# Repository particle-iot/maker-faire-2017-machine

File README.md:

# Maker Faire Machine

Welcome friends! Put all the amazing code, diagrams, PCB files and other
artifacts needed to build the Machine here.

# License

Copyright (C) 2017 Particle Industries Inc
All software code is licensed under the MIT license
All hardware designs are licensed under the Creative Commons Attribution-ShareAlike (CC-BY-SA) license

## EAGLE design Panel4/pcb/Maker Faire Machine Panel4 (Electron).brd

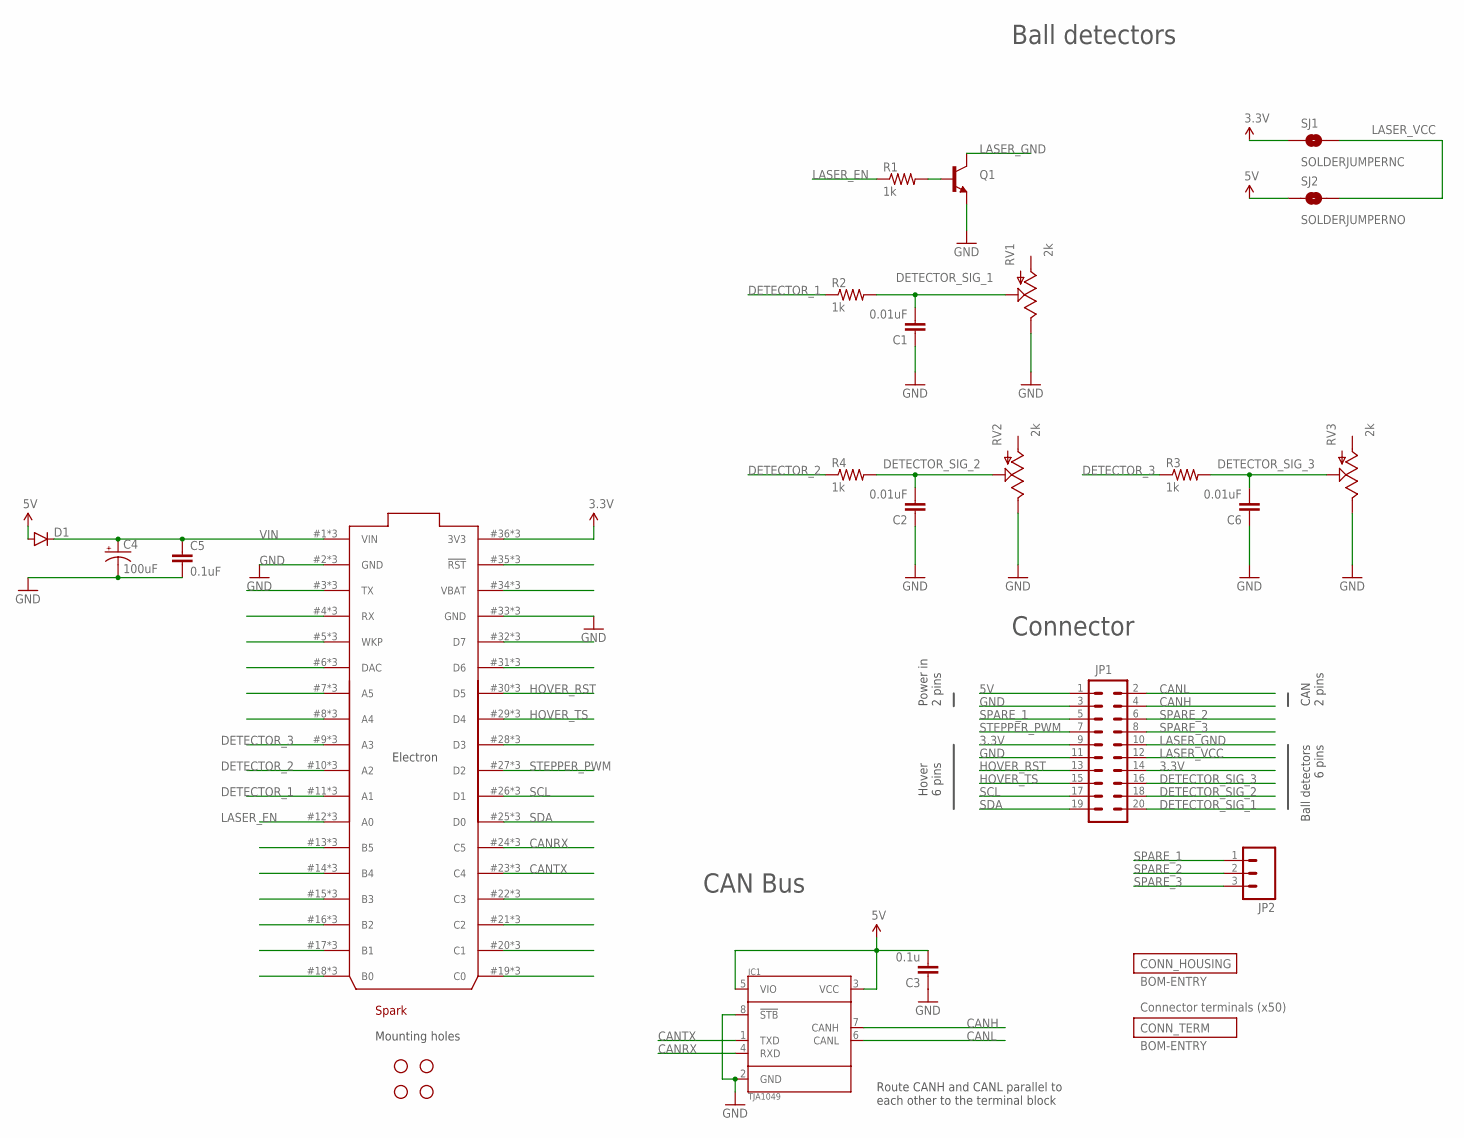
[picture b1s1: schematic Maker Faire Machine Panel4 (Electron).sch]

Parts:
C1, C2, C6: 0.01uF; 1206; PARTNO 12065C103KAT2A
C3: 0.1u; 1206; PARTNO 12065C104KAT2A
C4: 100uF; CPOL-RADIAL-100UF-25V; PARTNO EEU-FM1H101B
C5: 0.1uF; 1206; PARTNO 12065C104KAT2A
D1: DIODESMA; SMA-DIODE; PARTNO B230A-13-F
ELECTRON: ELECTRON_WITH_STACKABLE_HEADERS; ELECTRON_STACKABLE
IC1: TJA1049; SO8; PARTNO TJA1049T-118
JP1: M10X2_MMOLEX_MX150; 2X10_MOLEX_MX150; PARTNO 348302001
JP2: M031X03_NO_SILK; 1X03_NO_SILK
Q1: TRANSISTOR_NPNTO-92-AMMO; TO-92-AMMO; PARTNO PN2222ABU
R1, R2, R3, R4: 1k; 1206; PARTNO ERJ-8ENF1001V
RV1, RV2, RV3: 2k; 3362U; PARTNO 3362U-1-202LF
SJ1: SOLDERJUMPERNC; SJ_2S
SJ2: SOLDERJUMPERNO; SJ_2S-NO
STANDOFF1, STANDOFF2, STANDOFF3, STANDOFF4: STAND-OFF
U$2: SPARK_LOGOSILK; SPARK_LOGO_SILK

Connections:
3.3V: ELECTRON.36 (3V3), ELECTRON.#36 (3V3), ELECTRON.@36 (3V3), JP1.9, JP1.14, SJ1.1
5V: C3.2, D1.A, IC1.3 (VCC), IC1.5 (VIO), JP1.1, SJ2.1
CANH: IC1.7 (CANH), JP1.4
CANL: IC1.6 (CANL), JP1.2
CANRX: ELECTRON.24 (C5), ELECTRON.#24 (C5), ELECTRON.@24 (C5), IC1.4 (RXD)
CANTX: ELECTRON.23 (C4), ELECTRON.#23 (C4), ELECTRON.@23 (C4), IC1.1 (TXD)
DETECTOR_1: ELECTRON.11 (A1), ELECTRON.#11 (A1), ELECTRON.@11 (A1), R2.1
DETECTOR_2: ELECTRON.10 (A2), ELECTRON.#10 (A2), ELECTRON.@10 (A2), R4.1
DETECTOR_3: ELECTRON.9 (A3), ELECTRON.#9 (A3), ELECTRON.@9 (A3), R3.1
DETECTOR_SIG_1: C1.2, JP1.20, R2.2, RV1.P$2 (S)
DETECTOR_SIG_2: C2.2, JP1.18, R4.2, RV2.P$2 (S)
DETECTOR_SIG_3: C6.2, JP1.16, R3.2, RV3.P$2 (S)
GND: C1.1, C2.1, C3.1, C4.2 (-), C5.2, C6.1, ELECTRON.2 (GND), ELECTRON.33 (GND), ELECTRON.#2 (GND), ELECTRON.#33 (GND), ELECTRON.@2 (GND), ELECTRON.@33 (GND), IC1.2 (GND), IC1.8 (!STB), JP1.3, JP1.11, Q1.1 (E), RV1.P$1 (E), RV2.P$1 (E), RV3.P$1 (E)
HOVER_RST: ELECTRON.30 (D5), ELECTRON.#30 (D5), ELECTRON.@30 (D5), JP1.13
HOVER_TS: ELECTRON.29 (D4), ELECTRON.#29 (D4), ELECTRON.@29 (D4), JP1.15
LASER_EN: ELECTRON.12 (A0), ELECTRON.#12 (A0), ELECTRON.@12 (A0), R1.1
LASER_GND: JP1.10, Q1.3 (C)
LASER_VCC: JP1.12, SJ1.2, SJ2.2
unnamed: ELECTRON.35 (!RST), ELECTRON.#35 (!RST), ELECTRON.@35 (!RST)
unnamed: ELECTRON.34 (VBAT), ELECTRON.#34 (VBAT), ELECTRON.@34 (VBAT)
unnamed: Q1.2 (B), R1.2
unnamed: ELECTRON.32 (D7), ELECTRON.#32 (D7), ELECTRON.@32 (D7)
unnamed: ELECTRON.31 (D6), ELECTRON.#31 (D6), ELECTRON.@31 (D6)
unnamed: ELECTRON.28 (D3), ELECTRON.#28 (D3), ELECTRON.@28 (D3)
unnamed: ELECTRON.8 (A4), ELECTRON.#8 (A4), ELECTRON.@8 (A4)
unnamed: ELECTRON.7 (A5), ELECTRON.#7 (A5), ELECTRON.@7 (A5)
unnamed: ELECTRON.6 (DAC), ELECTRON.#6 (DAC), ELECTRON.@6 (DAC)
unnamed: ELECTRON.5 (WKP), ELECTRON.#5 (WKP), ELECTRON.@5 (WKP)
unnamed: ELECTRON.4 (RX), ELECTRON.#4 (RX), ELECTRON.@4 (RX)
unnamed: ELECTRON.3 (TX), ELECTRON.#3 (TX), ELECTRON.@3 (TX)
unnamed: ELECTRON.22 (C3), ELECTRON.#22 (C3), ELECTRON.@22 (C3)
unnamed: ELECTRON.21 (C2), ELECTRON.#21 (C2), ELECTRON.@21 (C2)
unnamed: ELECTRON.20 (C1), ELECTRON.#20 (C1), ELECTRON.@20 (C1)
unnamed: ELECTRON.19 (C0), ELECTRON.#19 (C0), ELECTRON.@19 (C0)
unnamed: ELECTRON.18 (B0), ELECTRON.#18 (B0), ELECTRON.@18 (B0)
unnamed: ELECTRON.17 (B1), ELECTRON.#17 (B1), ELECTRON.@17 (B1)
unnamed: ELECTRON.16 (B2), ELECTRON.#16 (B2), ELECTRON.@16 (B2)
unnamed: ELECTRON.15 (B3), ELECTRON.#15 (B3), ELECTRON.@15 (B3)
unnamed: ELECTRON.14 (B4), ELECTRON.#14 (B4), ELECTRON.@14 (B4)
unnamed: ELECTRON.13 (B5), ELECTRON.#13 (B5), ELECTRON.@13 (B5)
SCL: ELECTRON.26 (D1), ELECTRON.#26 (D1), ELECTRON.@26 (D1), JP1.17
SDA: ELECTRON.25 (D0), ELECTRON.#25 (D0), ELECTRON.@25 (D0), JP1.19
SPARE_1: JP1.5, JP2.1
SPARE_2: JP1.6, JP2.2
SPARE_3: JP1.8, JP2.3
STEPPER_PWM: ELECTRON.27 (D2), ELECTRON.#27 (D2), ELECTRON.@27 (D2), JP1.7
VIN: C4.1 (+), C5.1, D1.C, ELECTRON.1 (VIN), ELECTRON.#1 (VIN), ELECTRON.@1 (VIN)

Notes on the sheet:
Route CANH and CANL parallel to each other to the terminal block
Ball detectors
Hover 6 pins
CAN 2 pins
Ball detectors 6 pins
Connector
CAN Bus
Mounting holes
Power in 2 pins

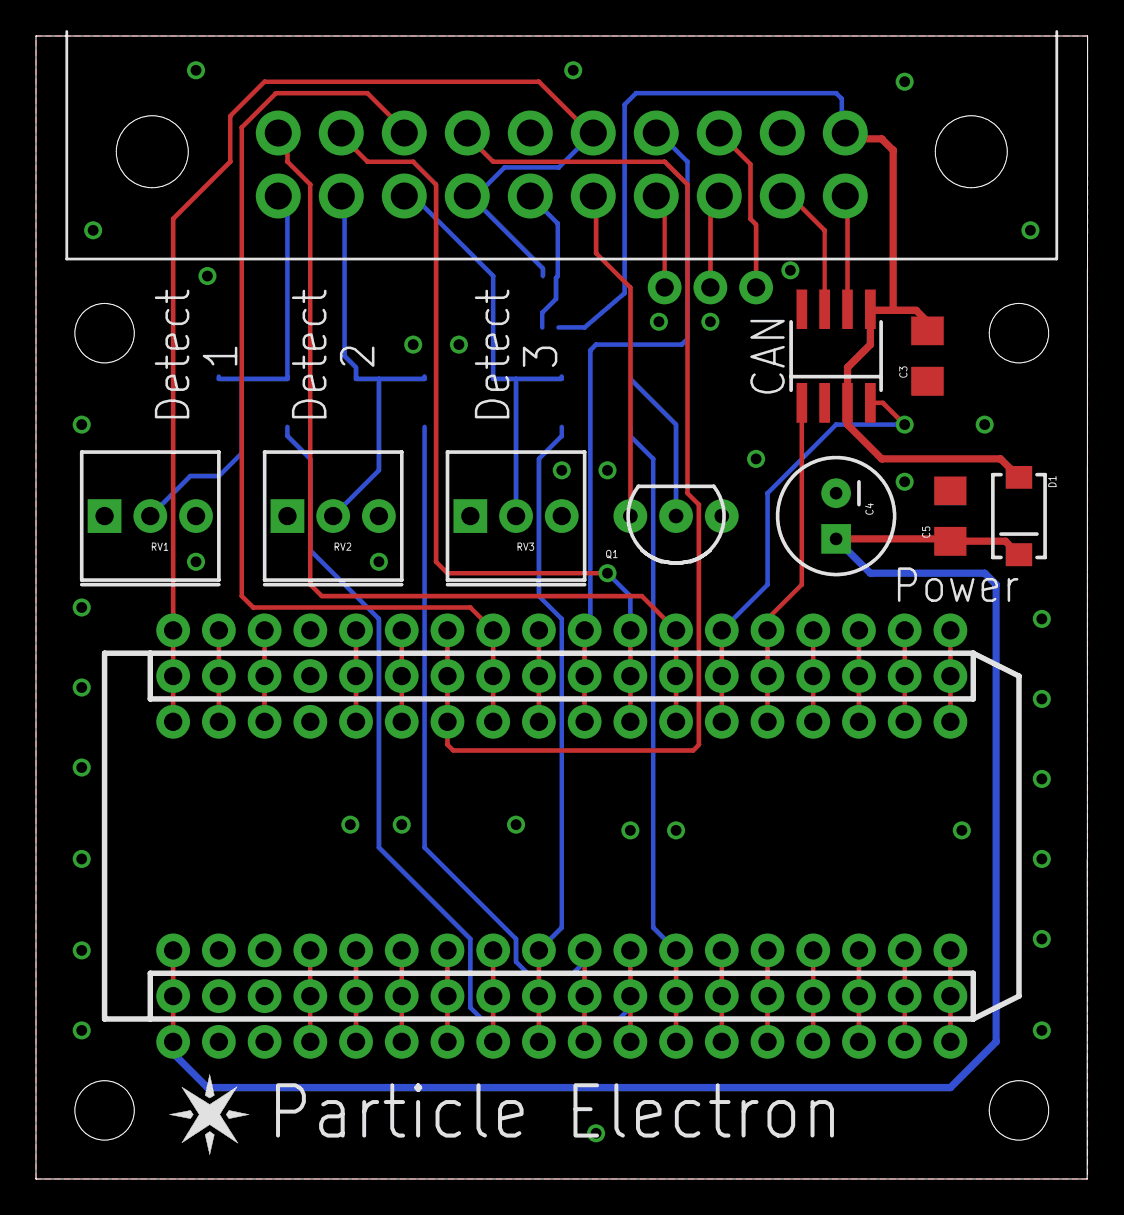
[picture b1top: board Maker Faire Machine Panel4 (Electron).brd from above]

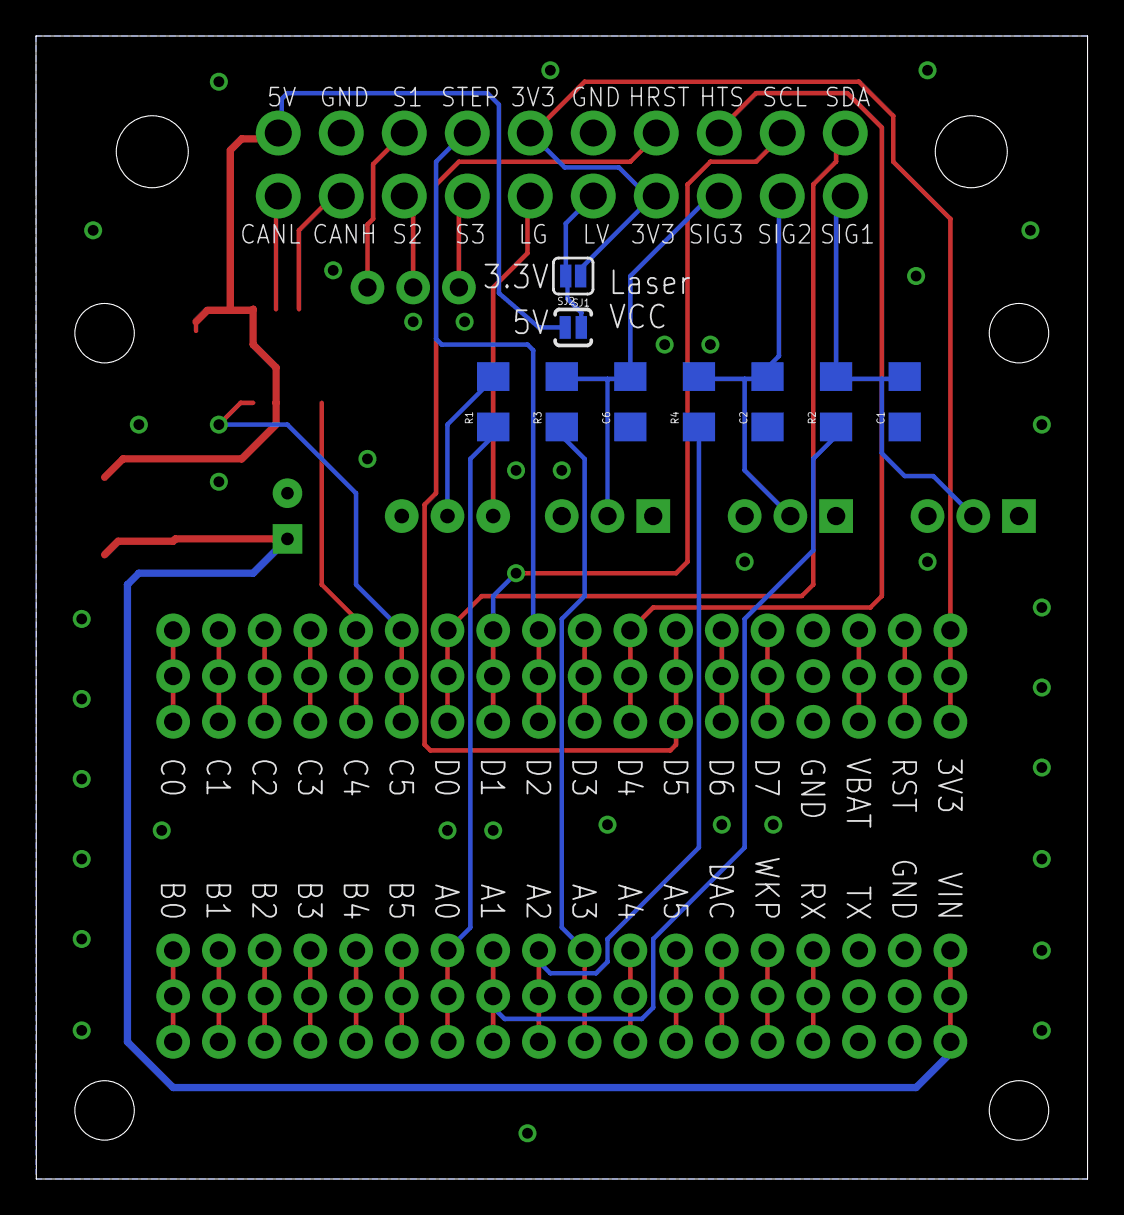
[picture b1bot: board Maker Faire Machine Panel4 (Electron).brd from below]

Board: 2 copper layers, 58.4 x 63.5 mm, 26 parts (9 on the bottom side), 47 nets.

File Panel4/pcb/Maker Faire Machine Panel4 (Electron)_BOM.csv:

Qty-1,Part References,Value,Package,Mfg Part Num,Mfg Name,VID,Vendor Part Num,Description,XREF
0,JP2(DNP),,1X03_NO_SILK,***PART# '*' NOT FOUND***,*,*,*,*,*
1,JP1,,2X10_MOLEX_MX150,348302001,Molex,DK,WM12752-ND,MX150 RA HDR 2X10 ST BLK KEY A,REF77
1,D1,,SMA-DIODE,B230A-13-F,Diodes-Incorporated,DK,B230A-FDICT-ND,DIODE SCHOTTKY 30V 2A SMA,REF43
1,Q1,,TO-92-AMMO,PN2222ABU,Fairchild Semiconductor ,DK,PN2222AFS-ND,TRANSISTOR NPN TO92,REF75
2,"C3, C5",0.1uF,1206,12065C104KAT2A,AVX,DK,478-1556-1-ND,CERAMIC CAPACITOR 0.1UF 50V X7R 10% 1206,REF61
3,"C1, C2, C6",0.01uF,1206,12065C103KAT2A,AVX,DK,478-1542-1-ND,MLCC CAPACITOR 0.01uF 50V X7R 10% 1206 FULL REEL,REF62
4,"R1, R2, R3, R4",1k,1206,ERJ-8ENF1001V,Panasonic,DK,P1.00KFCT-ND,RES SMD 1K OHM 1% 1/4W 1206,REF74
3,"RV1, RV2, RV3",2k,3362U,3362U-1-202LF,Bourns Inc.,DK,3362U-202LF-ND,TRIMMER 2K OHM 0.5W PC PIN,REF72
1,C4,100uF,CPOL-RADIAL-100UF-25V,EEU-FM1H101B,Panasonic Electronic Components,DK,P19712CT-ND,CAP ALUM 100UF 20% 50V RADIAL,REF76
50,CONN_TERM,BOM-ENTRY,*,330122002,Molex,DK,WM3687CT-ND,TERM RCPT TIN 18-20AWG SLD,REF79
1,CONN_HOUSING,BOM-ENTRY,*,334722001,Molex,DK,WM4737-ND,CONN RCPT 20POS DUAL BLACK,REF78
1,ELECTRON,ELECTRON_WITH_STACKABLE_HEADERS,ELECTRON_STACKABLE,***PART# '*' NOT FOUND***,*,*,*,*,*
1,IC1,TJA1049,SO8,TJA1049T-118,NXP Semiconductors,DK,568-8682-1-ND,IC CAN TRANSEIVER HS 8SOIC,REF16

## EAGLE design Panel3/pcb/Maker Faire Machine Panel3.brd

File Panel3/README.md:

# Panel 3

**Sensor:** Rotary encoder (quadrature)
**Mechanism:** ball lifter with multiple paths/runs
**Story:** Particle cloud routes and delivers the data internally

[See spreadsheet](https://docs.google.com/spreadsheets/d/1myQVK4iyX1niJGtPiAOqu2GMmV2cjAntq5kpxnjmFF0/edit#gid=340408367)
for more info.

## TOC

* Mechanical drawings
* BOM
* PCB
* Firmware
* Tweakable parameters

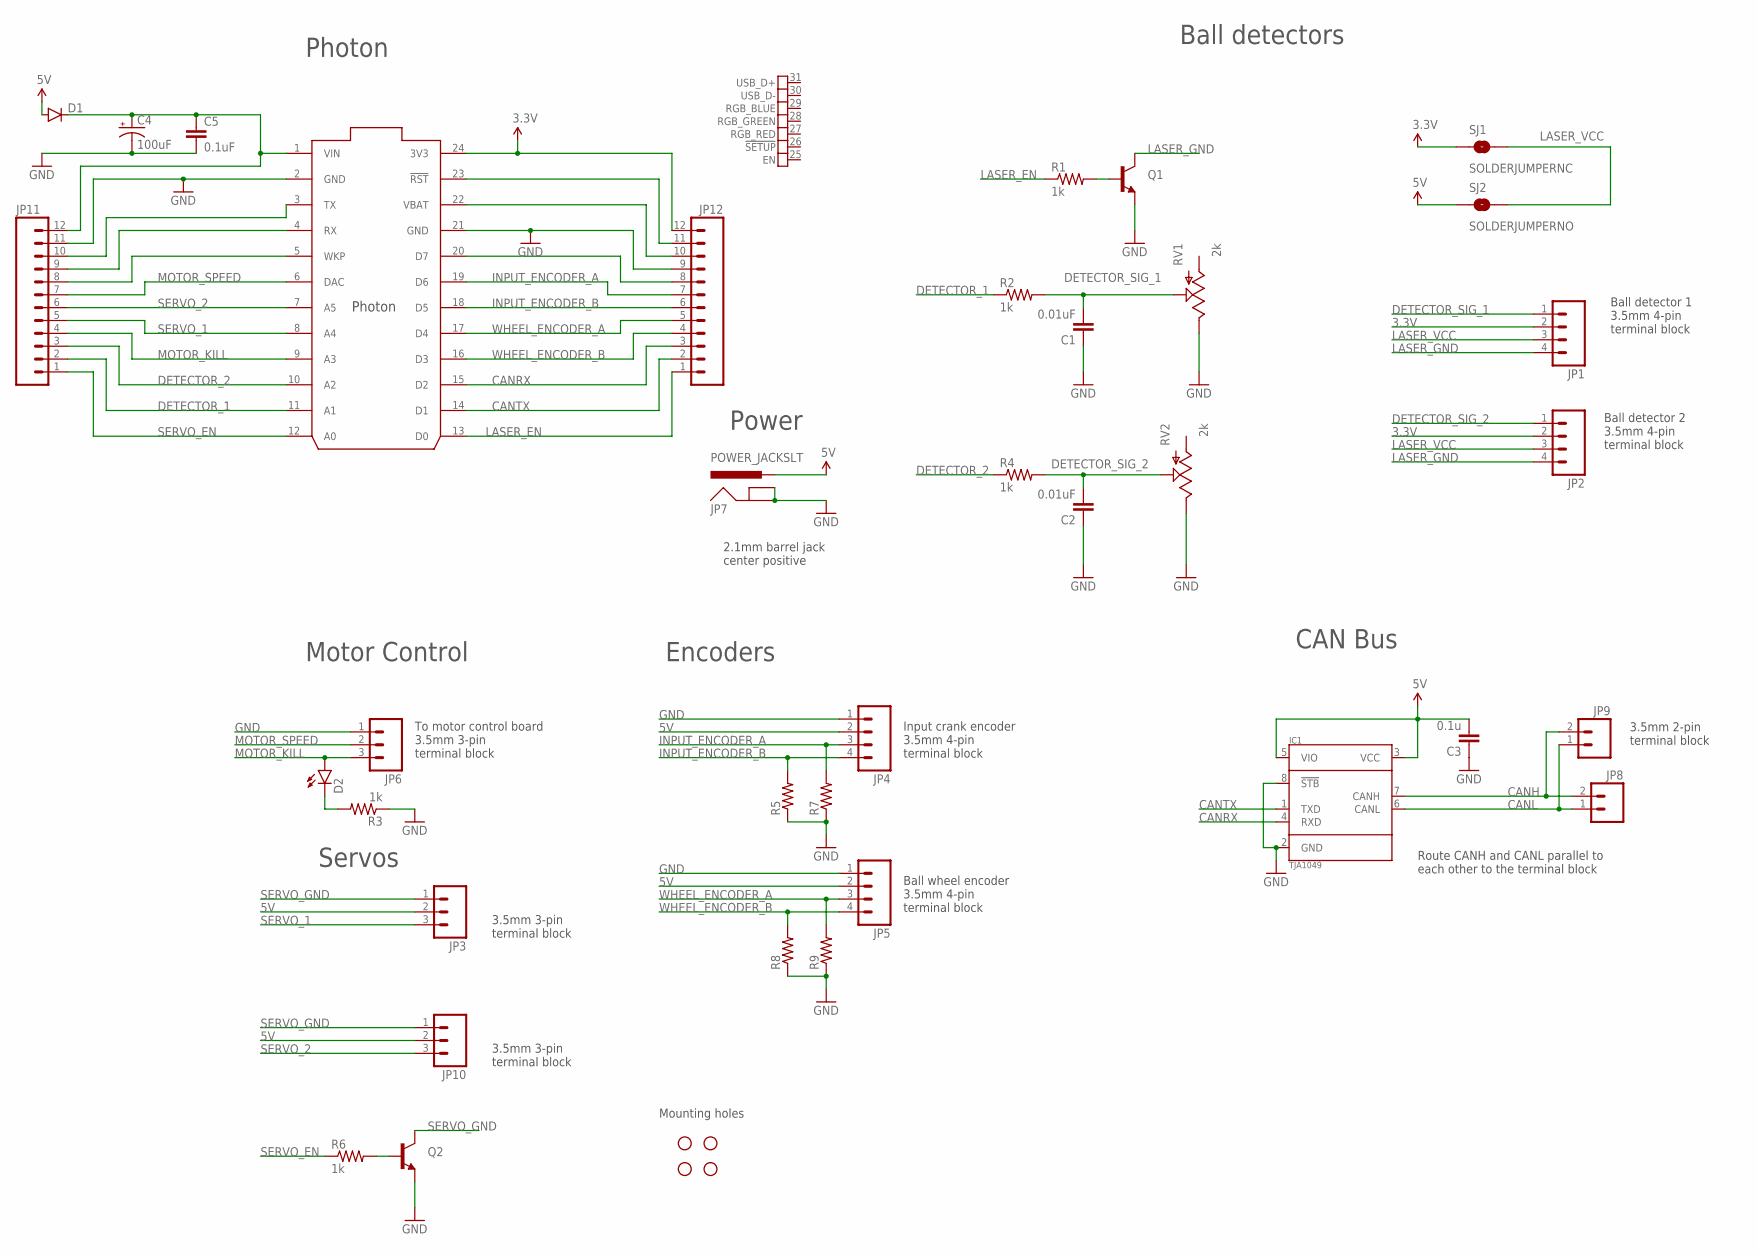
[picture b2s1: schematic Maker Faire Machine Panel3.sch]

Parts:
C1, C2: 0.01uF; 1206; PARTNO 12065C103KAT2A
C3: 0.1u; 1206; PARTNO 12065C104KAT2A
C4: 100uF; CPOL-RADIAL-100UF-25V; PARTNO EEU-FM1H101B
C5: 0.1uF; 1206; PARTNO 12065C104KAT2A
D1: DIODESMA; SMA-DIODE; PARTNO B230A-13-F
D2: LED5MM; PARTNO SSL-LX5093HD
IC1: TJA1049; SO8; PARTNO TJA1049T-118
JP1, JP2, JP4: M04SCREW; SCREWTERMINAL-3.5MM-4; PARTNO OSTTE040104
JP3, JP6: M03SCREW; SCREWTERMINAL-3.5MM-3; PARTNO OSTTE020104
JP5: M04SCREW; SCREWTERMINAL-3.5MM-4; PARTNO OSTTE030104
JP7: POWER_JACKSLT; POWER_JACK_SLOT; PARTNO PJ-202A
JP8, JP9: M023.5MM; SCREWTERMINAL-3.5MM-2; PARTNO OSTTE020104
JP10: M03SCREW; SCREWTERMINAL-3.5MM-3; PARTNO OSTTE030104
JP11, JP12: M12NO_SILK; 1X12_NO_SILK
Q1, Q2: TRANSISTOR_NPNTO-92-AMMO; TO-92-AMMO; PARTNO PN2222ABU
R1, R2, R3, R4, R6: 1k; 1206; PARTNO ERJ-8ENF1001V
R5, R7, R8, R9: RESISTORKIT; AXIAL-0.3-KIT
RV1, RV2: 2k; 3362U; PARTNO 3362U-1-202LF
SJ1: SOLDERJUMPERNC; SJ_2S
SJ2: SOLDERJUMPERNO; SJ_2S-NO
STANDOFF1, STANDOFF2, STANDOFF3, STANDOFF4: STAND-OFF
U$1: PHOTON_SMD

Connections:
3.3V: JP1.2, JP2.2, JP12.12, SJ1.1, U$1.24 (3V3)
5V: C3.2, D1.A, IC1.3 (VCC), IC1.5 (VIO), JP3.2, JP4.2, JP5.2, JP7.PWR, JP10.2, SJ2.1
CANH: IC1.7 (CANH), JP8.2, JP9.2
CANL: IC1.6 (CANL), JP8.1, JP9.1
CANRX: IC1.4 (RXD), JP12.3, U$1.15 (D2)
CANTX: IC1.1 (TXD), JP12.2, U$1.14 (D1)
DETECTOR_1: JP11.2, R2.1, U$1.11 (A1)
DETECTOR_2: JP11.3, R4.1, U$1.10 (A2)
DETECTOR_SIG_1: C1.2, JP1.1, R2.2, RV1.P$2 (S)
DETECTOR_SIG_2: C2.2, JP2.1, R4.2, RV2.P$2 (S)
GND: C1.1, C2.1, C3.1, C4.2 (-), C5.2, IC1.2 (GND), IC1.8 (!STB), JP4.1, JP5.1, JP6.1, JP7.GND@1 (GNDBREAK), JP7.GND@2 (GND), JP11.11, JP12.9, Q1.1 (E), Q2.1 (E), R3.1, R5.P$1 (1), R7.P$1 (1), R8.P$1 (1), R9.P$1 (1), RV1.P$1 (E), RV2.P$1 (E), U$1.2 (GND), U$1.21 (GND)
INPUT_ENCODER_A: JP4.3, JP12.7, R7.P$2 (2), U$1.19 (D6)
INPUT_ENCODER_B: JP4.4, JP12.6, R5.P$2 (2), U$1.18 (D5)
LASER_EN: JP12.1, R1.1, U$1.13 (D0)
LASER_GND: JP1.4, JP2.4, Q1.3 (C)
LASER_VCC: JP1.3, JP2.3, SJ1.2, SJ2.2
MOTOR_KILL: D2.A, JP6.3, JP11.4, U$1.9 (A3)
MOTOR_SPEED: JP6.2, JP11.7, U$1.6 (DAC)
unnamed: Q1.2 (B), R1.2
unnamed: Q2.2 (B), R6.2
unnamed: D2.K (C), R3.2
unnamed: JP12.8, U$1.20 (D7)
unnamed: JP12.10, U$1.22 (VBAT)
unnamed: JP12.11, U$1.23 (!RST)
RX: JP11.9, U$1.4 (RX)
SERVO_1: JP3.3, JP11.5, U$1.8 (A4)
SERVO_2: JP10.3, JP11.6, U$1.7 (A5)
SERVO_EN: JP11.1, R6.1, U$1.12 (A0)
SERVO_GND: JP3.1, JP10.1, Q2.3 (C)
TX: JP11.10, U$1.3 (TX)
VIN: C4.1 (+), C5.1, D1.C, JP11.12, U$1.1 (VIN)
WHEEL_ENCODER_A: JP5.3, JP12.5, R9.P$2 (2), U$1.17 (D4)
WHEEL_ENCODER_B: JP5.4, JP12.4, R8.P$2 (2), U$1.16 (D3)
WKP: JP11.8, U$1.5 (WKP)

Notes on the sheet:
Ball detectors
Ball detector 1 3.5mm 4-pin terminal block
Ball detector 2 3.5mm 4-pin terminal block
CAN Bus
Encoders
Route CANH and CANL parallel to each other to the terminal block
Input crank encoder 3.5mm 4-pin terminal block
Ball wheel encoder 3.5mm 4-pin terminal block
Motor Control
To motor control board 3.5mm 3-pin terminal block
Power
2.1mm barrel jack center positive
Photon
Servos
3.5mm 3-pin terminal block
Mounting holes
3.5mm 2-pin terminal block

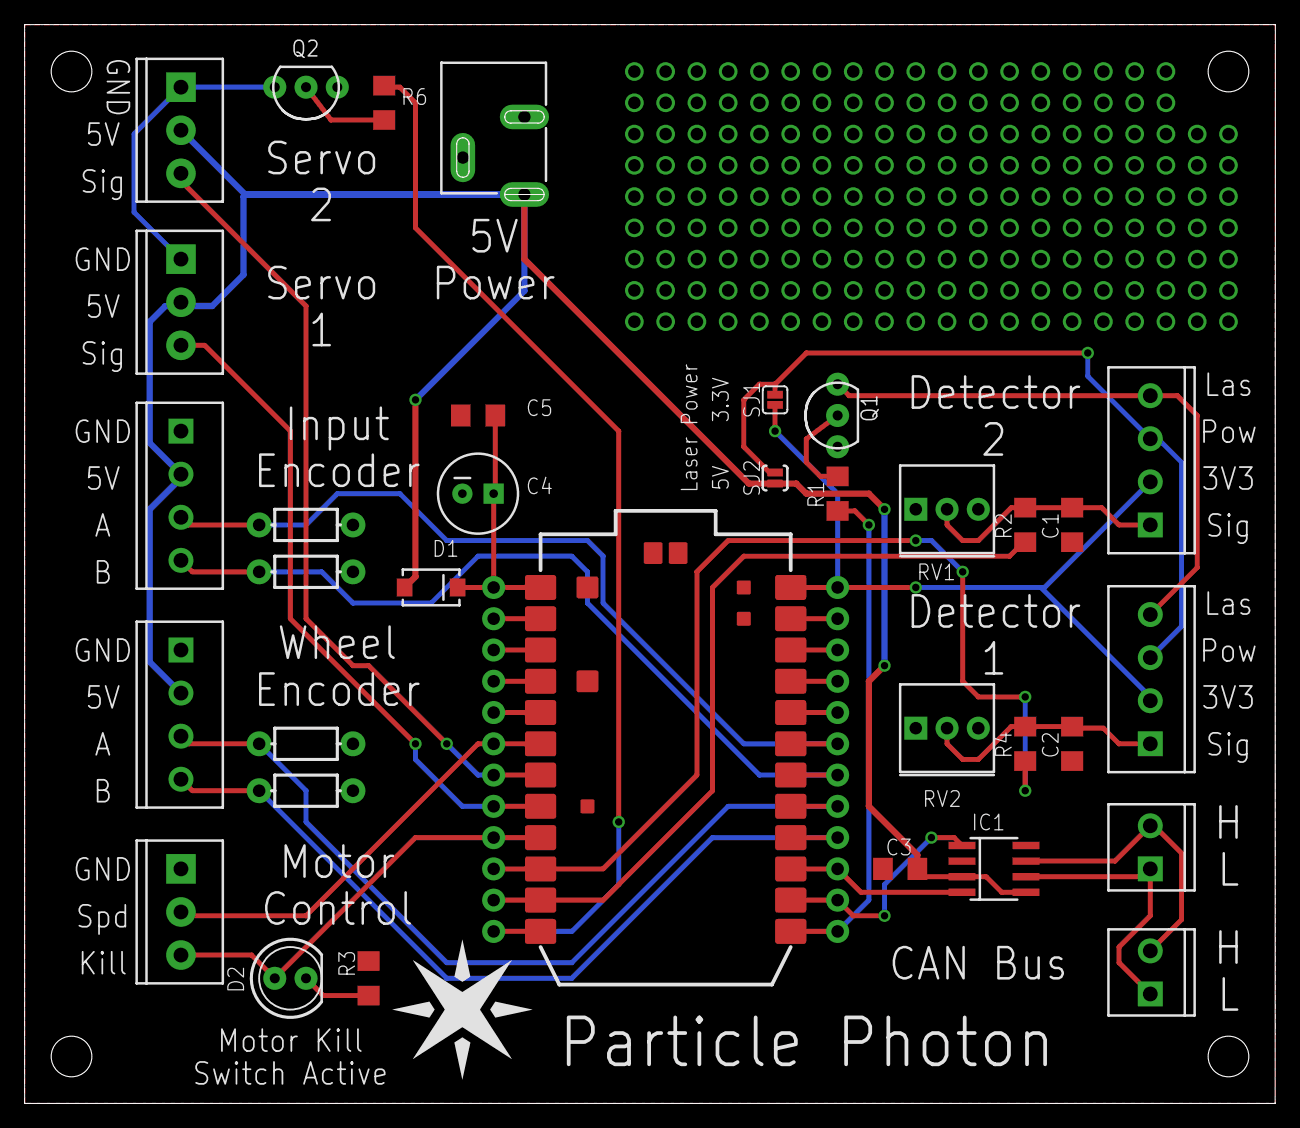
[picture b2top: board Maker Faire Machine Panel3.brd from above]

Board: 2 copper layers, 101.6 x 87.6 mm, 40 parts (0 on the bottom side), 34 nets.

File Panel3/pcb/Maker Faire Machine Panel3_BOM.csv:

Qty-1,Part References,Value,Package,Mfg Part Num,Mfg Name,VID,Vendor Part Num,Description,XREF
1,"D1",,SMA-DIODE,B230A-13-F,Diodes-Incorporated,DK,B230A-FDICT-ND,DIODE SCHOTTKY 30V 2A SMA,REF43
4,"JP3, JP6, JP8, JP9",,SCREWTERMINAL-3.5MM-2,OSTTE020104,On Shore Technology Inc.,DK,ED2740-ND,TERMINAL BLOCK 3.5MM 2POS PCB,REF68
2,"JP10, JP5",,SCREWTERMINAL-3.5MM-4,OSTTE030104,On Shore Technology Inc.,DK,ED2741-ND,TERMINAL BLOCK 3.5MM 3POS PCB,REF69
3,"JP1, JP2, JP4",,SCREWTERMINAL-3.5MM-4,OSTTE040104,On Shore Technology Inc.,DK,ED2742-ND,TERMINAL BLOCK 3.5MM 4POS PCB,REF70
2,"Q1, Q2",,TO-92,PN2222ABU,Fairchild Semiconductor ,DK,PN2222AFS-ND,TRANSISTOR NPN TO92,REF75
1,"D2",,LED5MM,SSL-LX5093HD,Lumex,DK,67-1102-ND,LED RED DIFF 5MM ROUND T/H,REF73
2,"C3, C5",0.1uF,1206,12065C104KAT2A,AVX,DK,478-1556-1-ND,CERAMIC CAPACITOR 0.1UF 50V X7R 10% 1206,REF61
2,"C1, C2",0.01uF,1206,12065C103KAT2A,AVX,DK,478-1542-1-ND,MLCC CAPACITOR 0.01uF 50V X7R 10% 1206 FULL REEL,REF62
5,"R1, R2, R3, R4, R6",1k,1206,ERJ-8ENF1001V,Panasonic,DK,P1.00KFCT-ND,RES SMD 1K OHM 1% 1/4W 1206,REF74
2,"RV1, RV2",2k,3362U,3362U-1-202LF,Bourns Inc.,DK,3362U-202LF-ND,TRIMMER 2K OHM 0.5W PC PIN,REF72
1,"C4",100uF,CPOL-RADIAL-100UF-25V,EEU-FM1H101B,Panasonic Electronic Components,DK,P19712CT-ND,CAP ALUM 100UF 20% 50V RADIAL,REF76
1,"U$1",PHOTON_SMD,PHOTON_SMD,***PART# '*' NOT FOUND***,*,*,*,*,*
1,"JP7",POWER_JACKSLT,POWER_JACK_SLOT,PJ-202A,CUI Inc.,DK,CP-202A-ND,CONN PWR JACK 2X5.5MM KINKED PIN,REF71
1,"IC1",TJA1049,SO8,TJA1049T-118,NXP Semiconductors,DK,568-8682-1-ND,IC CAN TRANSEIVER HS 8SOIC,REF16

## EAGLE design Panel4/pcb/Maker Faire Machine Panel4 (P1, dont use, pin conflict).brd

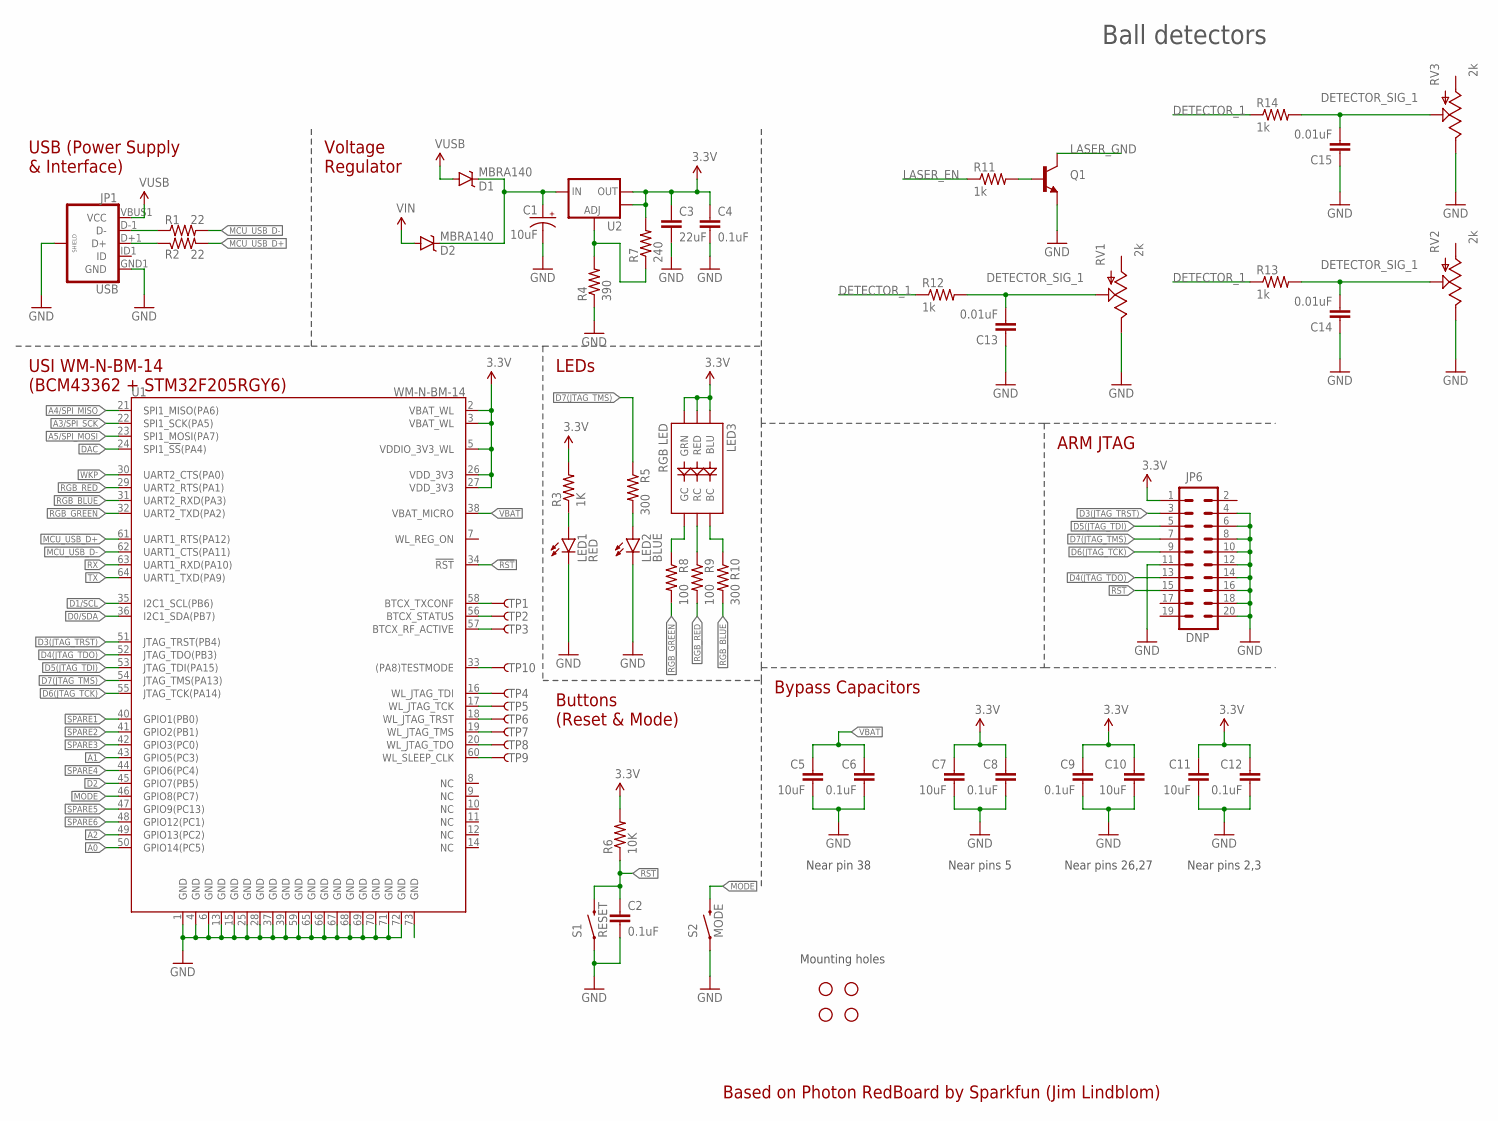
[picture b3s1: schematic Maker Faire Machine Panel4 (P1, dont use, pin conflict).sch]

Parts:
C1: 10uF; EIA3216
C2, C4, C6, C8, C9, C12: 0.1uF; 0603-CAP
C3: 22uF; 0805
C5, C7, C10, C11: 10uF; 0603-CAP
C13, C14, C15: 0.01uF; 1206; PARTNO 12065C103KAT2A
D1, D2: MBRA140; SMA-DIODE
JP1: USB; USB-B-MICRO-SMD_V03
JP6: DNP; 2X10
LED1: RED; LED-1206
LED2: BLUE; LED-1206
LED3: RGB LED; PLCC-6-LED
Q1: TRANSISTOR_NPNSOT89; SOT89; PARTNO PN2222ABU
R1, R2: 22; 0603-RES
R3: 1K; 0603-RES
R4: 390; 0603-RES
R5, R10: 300; 0603-RES
R6: 10K; 0603-RES
R7: 240; 0603-RES
R8, R9: 100; 0603-RES
R11, R12, R13, R14: 1k; 1206; PARTNO ERJ-8ENF1001V
RV1, RV2, RV3: 2k; 3362U; PARTNO 3362U-1-202LF
S1: RESET; TACTILE-PTH
S2: MODE; TACTILE-PTH
STANDOFF1, STANDOFF2, STANDOFF3, STANDOFF4: STAND-OFF
TP1, TP2, TP3, TP4, TP5, TP6, TP7, TP8, TP9, TP10: TEST-POINTTP_15TH_THRU; TP_15TH
U1: WM-N-BM-14
U2: V_REG_LM1117SOT223; SOT223

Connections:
3.3V: C3.1, C4.1, C7.1, C8.1, C9.1, C10.1, C11.1, C12.1, JP6.1, LED3.AB (BLU), LED3.AG (GRN), LED3.AR (RED), R3.2, R6.2, R7.2, U1.2 (VBAT_WL), U1.3 (VBAT_WL), U1.5 (VDDIO_3V3_WL), U1.26 (VDD_3V3), U1.27 (VDD_3V3), U2.2 (OUT), U2.4 (OUT)
!MODE: S2.3 (2), U1.46 (GPIO8(PC7))
!RST: C2.1, JP6.15, R6.1, S1.3 (2), U1.34 (!RST!)
A0: U1.50 (GPIO14(PC5))
A1: U1.43 (GPIO5(PC3))
A2: U1.49 (GPIO13(PC2))
A3/SPI_SCK: U1.22 (SPI1_SCK(PA5))
A4/SPI_MISO: U1.21 (SPI1_MISO(PA6))
A5/SPI_MOSI: U1.23 (SPI1_MOSI(PA7))
BTCX_RF_ACTIVE: TP3.P$1, U1.57 (BTCX_RF_ACTIVE)
BTCX_STATUS: TP2.P$1, U1.56 (BTCX_STATUS)
BTCX_TXCONF: TP1.P$1, U1.58 (BTCX_TXCONF)
D0/SDA: U1.36 (I2C1_SDA(PB7))
D1/SCL: U1.35 (I2C1_SCL(PB6))
D2: U1.45 (GPIO7(PB5))
D3(JTAG_TRST): JP6.3, U1.51 (JTAG_TRST(PB4))
D4(JTAG_TDO): JP6.13, U1.52 (JTAG_TDO(PB3))
D5(JTAG_TDI): JP6.5, U1.53 (JTAG_TDI(PA15))
D6(JTAG_TCK): JP6.9, U1.55 (JTAG_TCK(PA14))
D7(JTAG_TMS): JP6.7, R5.1, U1.54 (JTAG_TMS(PA13))
D+: JP1.D+1 (D+), R2.1
D-: JP1.D-1 (D-), R1.1
DAC: U1.24 (SPI1_!SS!(PA4))
DETECTOR_1: R12.1, R13.1, R14.1
DETECTOR_SIG_1: C13.2, C14.2, C15.2, R12.2, R13.2, R14.2, RV1.P$2 (S), RV2.P$2 (S), RV3.P$2 (S)
GND: C1.C (-), C2.2, C3.2, C4.2, C5.2, C6.2, C7.2, C8.2, C9.2, C10.2, C11.2, C12.2, C13.1, C14.1, C15.1, JP1.GND1 (GND), JP1.SHIELD1 (SHIELD), JP1.SHIELD2 (SHIELD), JP1.SHIELD3 (SHIELD), JP6.4, JP6.6, JP6.8, JP6.10, JP6.11, JP6.12, JP6.14, JP6.16, JP6.18, JP6.20, LED1.C, LED2.C, Q1.3 (E), R4.1, RV1.P$1 (E), RV2.P$1 (E), RV3.P$1 (E), S1.1, S2.1, U1.1 (GND), U1.4 (GND), U1.6 (GND), U1.13 (GND), U1.15 (GND), U1.25 (GND), U1.28 (GND), U1.37 (GND), U1.39 (GND), U1.59 (GND), U1.65 (GND), U1.66 (GND), U1.67 (GND), U1.68 (GND), U1.69 (GND), U1.70 (GND), U1.71 (GND), U1.72 (GND)
LASER_EN: R11.1
LASER_GND: Q1.2 (C)
MCU_USB_D+: R2.2, U1.61 (UART1_RTS(PA12))
MCU_USB_D-: R1.2, U1.62 (UART1_CTS(PA11))
unnamed: TP10.P$1, U1.33 ((PA8)TESTMODE)
unnamed: LED3.CG (GC), R8.1
unnamed: LED3.CR (RC), R9.1
unnamed: LED3.CB (BC), R10.1
unnamed: LED1.A, R3.1
unnamed: LED2.A, R5.2
unnamed: Q1.1 (B), R11.2
unnamed: C1.A (+), D1.C, D2.C, U2.3 (IN)
unnamed: R4.2, R7.1, U2.1 (ADJ)
RGB_BLUE: R10.2, U1.31 (UART2_RXD(PA3))
RGB_GREEN: R8.2, U1.32 (UART2_TXD(PA2))
RGB_RED: R9.2, U1.29 (UART2_RTS(PA1))
RX: U1.63 (UART1_RXD(PA10))
SPARE1: U1.40 (GPIO1(PB0))
SPARE2: U1.41 (GPIO2(PB1))
SPARE3: U1.42 (GPIO3(PC0))
SPARE4: U1.44 (GPIO6(PC4))
SPARE5: U1.47 (GPIO9(PC13))
SPARE6: U1.48 (GPIO12(PC1))
TX: U1.64 (UART1_TXD(PA9))
VBAT: C5.1, C6.1, U1.38 (VBAT_MICRO)
VIN: D2.A
VUSB: D1.A, JP1.VBUS1 (VCC)
WKP: U1.30 (UART2_CTS(PA0))
WL_JTAG_TCK: TP5.P$1, U1.17 (WL_JTAG_TCK)
WL_JTAG_TDI: TP4.P$1, U1.16 (WL_JTAG_TDI)
WL_JTAG_TDO: TP8.P$1, U1.20 (WL_JTAG_TDO)
WL_JTAG_TMS: TP7.P$1, U1.19 (WL_JTAG_TMS)
WL_JTAG_TRST: TP6.P$1, U1.18 (WL_JTAG_TRST)
WL_SLEEP_CLK: TP9.P$1, U1.60 (WL_SLEEP_CLK)

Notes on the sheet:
Near pin 38
Near pins 26,27
Near pins 5
Near pins 2,3
Voltage Regulator
USB (Power Supply & Interface)
ARM JTAG
Bypass Capacitors
LEDs
Buttons (Reset & Mode)
USI WM-N-BM-14 (BCM43362 + STM32F205RGY6)
Based on Photon RedBoard by Sparkfun (Jim Lindblom)
Mounting holes
Ball detectors

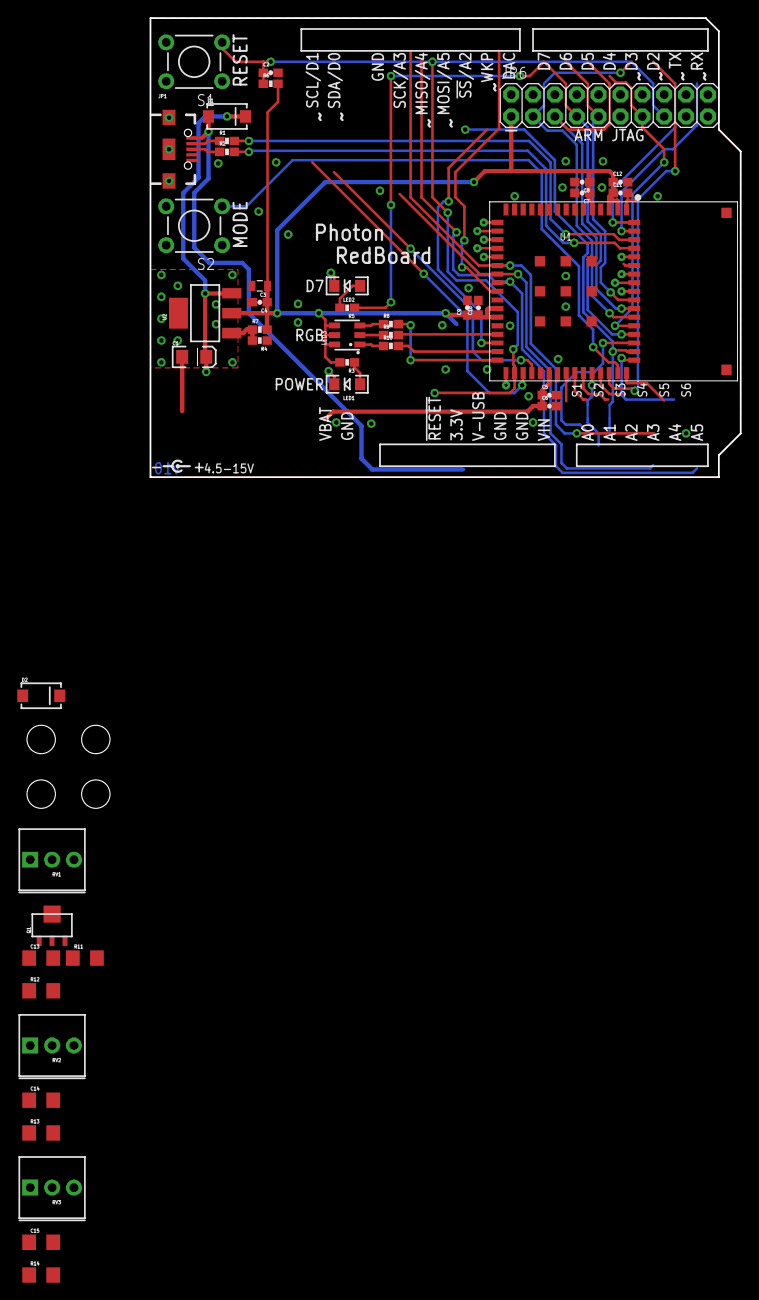
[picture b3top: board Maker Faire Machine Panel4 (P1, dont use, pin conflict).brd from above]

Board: 2 copper layers, 68.6 x 53.3 mm, 58 parts (1 on the bottom side), 38 nets.

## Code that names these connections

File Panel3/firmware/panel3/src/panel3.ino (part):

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const auto BALL_DETECTOR_2_PIN = A1;
const auto BALL_DETECTOR_1_PIN = A2;
const auto BALL_WHEEL_KILL_SWITCH_PIN = A3;
const auto SERVO_1_PIN = A4;
const auto SERVO_2_PIN = A5;
const auto BALL_WHEEL_MOTOR_SPEED_PIN = DAC;
const auto BALL_DETECTOR_3_PIN = WKP;
const auto WHEEL_TURN_PIN = TX;

/*
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 */

const auto MOTOR_RUN = HIGH;
const auto MOTOR_KILL = LOW;

auto motorState = AUTO_START ? MOTOR_RUN : MOTOR_KILL;
uint32_t motorSpeed = 0;
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
void setupMotor() {
  pinMode(BALL_WHEEL_KILL_SWITCH_PIN, OUTPUT);
  digitalWrite(BALL_WHEEL_KILL_SWITCH_PIN, MOTOR_KILL);
  pinMode(BALL_WHEEL_MOTOR_SPEED_PIN, OUTPUT);
  pinMode(WHEEL_TURN_PIN, INPUT_PULLUP);
}
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} doorState = DOORS_CLOSED;

void setupServos() {
  servo1.attach(SERVO_1_PIN);
  servo2.attach(SERVO_2_PIN);
  pinMode(SERVO_ENABLE_PIN, OUTPUT);
  digitalWrite(SERVO_ENABLE_PIN, SERVO_KILL);
}
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
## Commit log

2017-03-27 Prototype for Overview Display
2017-03-27 add run instructions
2017-04-17 Add firmware libraries
2017-04-17 add description of communication module
2017-04-18 Add lighting module code
2017-04-19 CAN library working
2017-04-22 Add HSV lib and lighting research
2017-04-22 describe hsv lib
2017-04-22 Update to lastest comms lib
2017-04-23 WIP multiple panel support in lighting
2017-04-23 Add active pattern for panel 2
2017-04-23 Add active mode for panel 3
2017-04-24 Add active pattern for panel 4
2017-04-24 Allow longer lighting delays
2017-04-25 Add active mode for panel 1 and tester
2017-04-25 Add WIP directory for Module 3
2017-04-25 Add 300 lights mode
2017-04-25 Add test firmwares
2017-04-26 Remove duplicate encoder test firmware
2017-04-26 Update encoder interrupt to use direct memory access to pin
2017-04-26 Don't read global multiple times in function
2017-04-26 Move pattern research firmware
2017-04-26 Move hero
2017-04-28 Update lighting code for protoboard
2017-04-29 add libraries
2017-04-29 add ball detector instructions
2017-04-29 Fix image
2017-04-29 Fix image again
2017-04-29 Add missing wire
2017-04-29 add detector assembled image
2017-04-29 add drill tip
2017-04-29 add detector bracket STL model
2017-04-29 add 3d printer settings
2017-05-01 Add Encoder library
2017-05-02 Move Panel3
2017-05-02 Add panel 3 firmware draft
2017-05-02 Update panel 3 firmware
2017-05-04 Draft of schematic for panel 3
2017-05-04 Add 2nd CAN terminal block for ease of wiring
2017-05-04 Increase cutoff frequency of ball detector lowpass
2017-05-04 Finished Panel 3 PCB Layout
2017-05-04 Add Gerbers
2017-05-04 Update panel 3 PDF schematics
2017-05-05 Update Panel 3 PCB after Eric's comments
2017-05-07 Add hero display firmware
2017-05-07 Add CAN implementation for Raspberry Pi
2017-05-08 Working firmware for hero display
2017-05-08 Fix LED orientation
2017-05-08 Panel 4 PCB work in progress
2017-05-08 First version of panel 4 PCB done
2017-05-09 Update libraries to latest
2017-05-09 Wired up Hero firmware to website to output JSON
2017-05-09 Website for hero display
2017-05-09 Tweaks to Hero firmware
2017-05-11 Add round ball detector
2017-05-11 Move holes in round ball detector
2017-05-11 Add round detector B
2017-05-11 Add DigiKey BOM for panel 4
2017-05-11 Show start/stop state
2017-05-11 Updates to panel 3 firmware
2017-05-11 Fix typo in Lighting code
2017-05-11 Update firmware for panel 3
2017-05-13 stop when you hit the edge, but allow it to go the other direction
2017-05-13 adding printer firmware
2017-05-16 updating images
2017-05-16 got the laser gates working enough for testing
2017-05-16 adding images
2017-05-16 adding "touch for ball", and "dispense when full" behaviors
2017-05-16 Finish Panel 3 firmware
2017-05-16 Panel1 firmware WIP
2017-05-16 Panel 1 firmware
2017-05-16 Finish panel 1 firmware
2017-05-16 Add control panel graphics
2017-05-17 Panel 2 firmware
2017-05-17 Rotating arrow
2017-05-17 Panel 1 lights
2017-05-17 Add font for hero
2017-05-17 Update SVG rendering code
2017-05-17 WIP firmware panel 2
2017-05-17 Change colors to make numbers pop more on Hero SVG
2017-05-17 Panel 2 firmware done
2017-05-17 updating wiring notes, build scripts
2017-05-17 Rename SVG segments to match machine
2017-05-17 cleanup,
2017-05-17 Map CAN to hero display
2017-05-17 fix hero
2017-05-17 Init display
2017-05-17 Hero
2017-05-17 adding can tester
2017-05-18 Update panel 1 and panel 2
2017-05-18 Add logs
2017-05-18 breathing code
2017-05-18 adding can bus tester
2017-05-18 adding new images
2017-05-18 adding laser gates / CAN print command
2017-05-18 updating baud, adding can-lib to hover controller,
2017-05-18 adding can bus transmit / recieve / counters / libs
2017-05-18 Firmware updates
2017-05-18 Finished panel 1 firmware
2017-05-18 Add button to turn wheel
2017-05-18 mostly working except CAN bus
2017-05-18 final updates to panel1
2017-05-19 Hair on fire update!
2017-05-19 Updates to hero
2017-05-19 Mapping hero display
2017-05-20 fixing ball pump hardware with software
2017-05-20 hover controls working
2018-01-03 org-rename
2018-01-26 Add license
2018-03-01 adding anything missing
2025-08-20 Add MIT license

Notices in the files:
parts and their libraries:
SparkFun-Passives: Licensing: Creative Commons ShareAlike 4.0 International - https://creativecommons.org/licenses/by-sa/4.0
Particle-Devices: Licensing: Designed by Particle.
bom: Copyright (C) 2010, Bob Starr
